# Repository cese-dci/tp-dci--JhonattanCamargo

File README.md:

# TP Diseño de Circuitos Imprsos [CESE 8Co2019 DCI]
## Autor: Jhonattan Camargo
### Alumno revisor: Fabián Sarmiento
### Descripción del proyecto:

El proyecto consiste en la elaboración de uno de los módulos del proyecto final de carrera. El módulo incorpora el integrado LP5012 de Texas Instruments, el cual es un controlador de leds de 12 canales, controlado a través de I2C. El módulo que se propone para el TP final es una adaptación al módulo de evaluación de TI LP5012EVM (http://www.ti.com/lit/ug/slvubb2/slvubb2.pdf) adaptado para ocupar poco espacio e incoporar 2 LEDs RGB y 6 leds individuales.

El repositorio está organizado de la siguiente forma:
  
  - Directorio “doc”: contiene la explicación del circuito, licencia y las revisiones realizadas al diseño.
  - Directorio “info”: contiene hojas de datos, y toda la información relevante como fotos o notas de aplicación.
  - Directorio “pcb”: archivos del proyecto Kicad.
    - Subdirectorio “3dshapes”: contiene los modelos 3D.

### Renders del proyecto:

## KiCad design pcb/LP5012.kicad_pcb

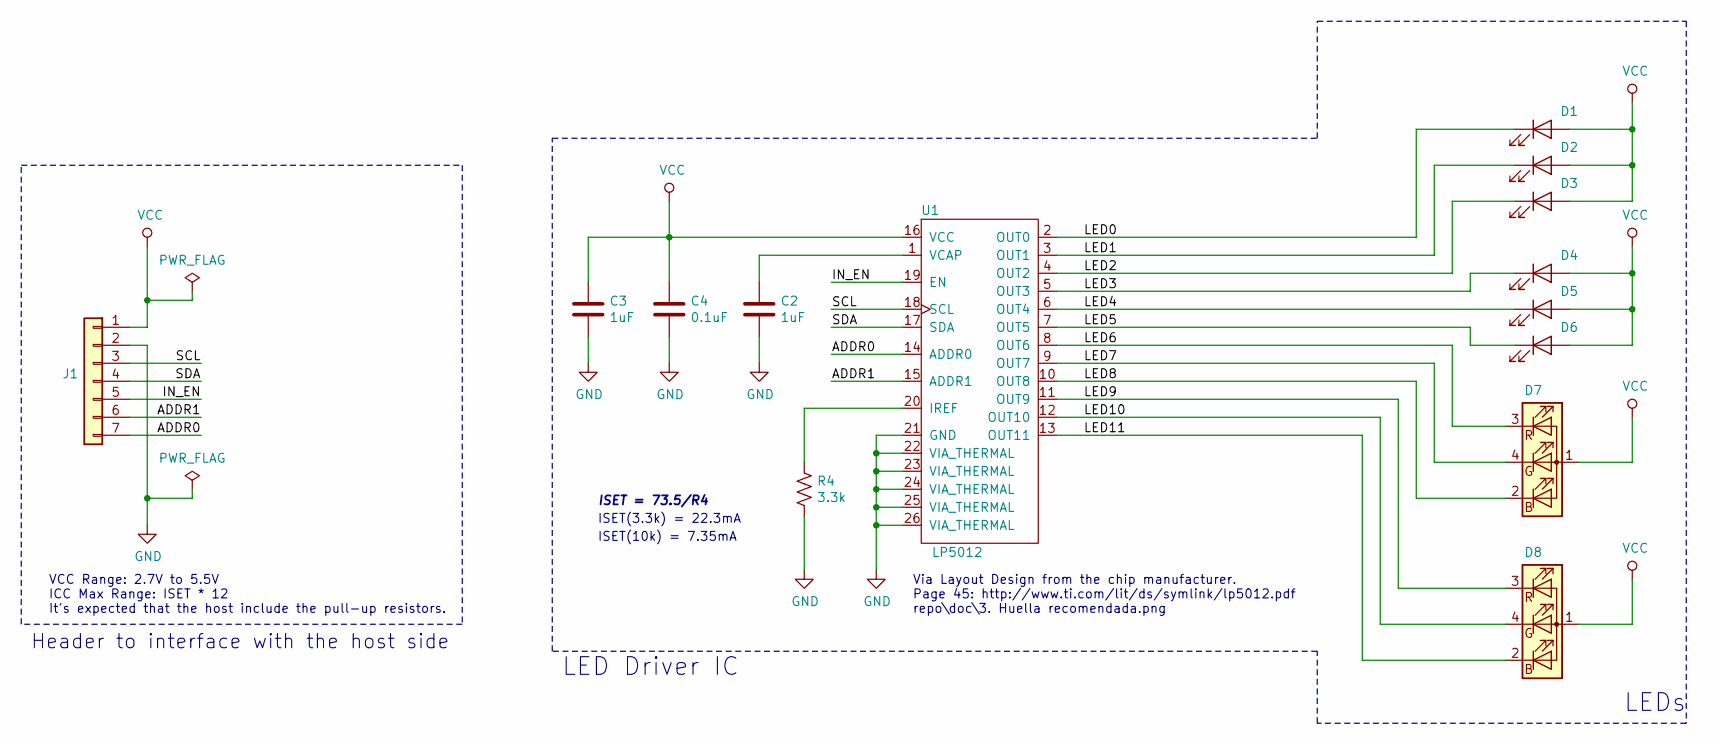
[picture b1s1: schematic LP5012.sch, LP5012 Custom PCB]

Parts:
C2, C3: 1uF; C_0805_2012Metric
C4: 0.1uF; C_0805_2012Metric
D1, D2, D3, D4, D5, D6: LED; LED_0805_2012Metric
D7, D8: LED_RGB; LED_RGB_1210_with3DShape
J1: Main Connector; PinHeader_1x07_P2.54mm_Vertical
R4: 3.3k; R_0805_2012Metric
U1: LP5012

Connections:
/ADDR0: J1.7, U1.14 (ADDR0)
/ADDR1: J1.6, U1.15 (ADDR1)
/IN_EN: J1.5, U1.19 (EN)
/LED0: D1.1 (K), U1.2 (OUT0)
/LED1: D2.1 (K), U1.3 (OUT1)
/LED2: D3.1 (K), U1.4 (OUT2)
/LED3: D4.1 (K), U1.5 (OUT3)
/LED4: D5.1 (K), U1.6 (OUT4)
/LED5: D6.1 (K), U1.7 (OUT5)
/LED6: D7.3 (RK), U1.8 (OUT6)
/LED7: D7.4 (GK), U1.9 (OUT7)
/LED8: D7.2 (BK), U1.10 (OUT8)
/LED9: D8.3 (RK), U1.11 (OUT9)
/LED10: D8.4 (GK), U1.12 (OUT10)
/LED11: D8.2 (BK), U1.13 (OUT11)
/SCL: J1.3, U1.18 (SCL)
/SDA: J1.4, U1.17 (SDA)
GND: C2.2, C3.2, C4.2, J1.2, R4.2, U1.21 (GND), U1.22 (VIA_THERMAL), U1.23 (VIA_THERMAL), U1.24 (VIA_THERMAL), U1.25 (VIA_THERMAL), U1.26 (VIA_THERMAL)
unnamed: C2.1, U1.1 (VCAP)
unnamed: R4.1, U1.20 (IREF)
VCC: C3.1, C4.1, D1.2 (A), D2.2 (A), D3.2 (A), D4.2 (A), D5.2 (A), D6.2 (A), D7.1 (A), D8.1 (A), J1.1, U1.16 (VCC)

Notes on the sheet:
Via Layout Design from the chip manufacturer. Page 45: http://www.ti.com/lit/ds/symlink/lp5012.pdf repo\doc\3. Huella recomendada.png
VCC Range: 2.7V to 5.5V ICC Max Range: ISET * 12 It's expected that the host include the pull-up resistors.
ISET = 73.5/R4
ISET(3.3k) = 22.3mA
Header to interface with the host side
LED Driver IC
LEDs
ISET(10k) = 7.35mA

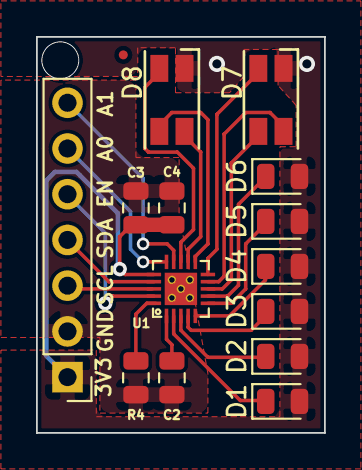
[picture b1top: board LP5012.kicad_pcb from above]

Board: 2 copper layers, 16.0 x 22.0 mm, 15 parts (0 on the bottom side), 21 nets.

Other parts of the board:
FD1: Fiducial_0.5mm_Mask1mm

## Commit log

2019-10-01 Inclusión de Esquemático V1
2019-10-04 Inclusión de la versión custom que se fabricará para el proyecto final
2019-10-04 Inclusion de datasheet del chip y otros archivos
2019-10-04 Corrección de errores y actualizacion de nombres
2019-10-05 Corregidos algunos aspectos del revisor
2019-10-06 Inclusion de PCB
2019-10-06 Avance de ruteo
2019-10-12 Inclusión de avance de PCB
    Inclusión de planos, queda pendiente agregar modelos 3D de agunos componentes
2019-10-12 Corrección de DRCs
2019-10-12 Inclusión de algunos aspectos de la corrección del compañero
2019-10-13 Depuración de archivos sobrantes y estructuración de carpetas
    Se añaden carpetas doc, info y pcb.
    Se limpian archivos que estaban de más.
2019-10-13 Creación de Readme.md
2019-10-13 Inclusión de modelos 3D y modificación de algunas liberías
2019-10-13 Inclusión de renders
2019-10-19 Ligeras modificaciones estéticas
2019-10-19 Inlcusión de notas de fabricación
2019-10-19 Update LP5012.kicad_pcb-bak
2019-10-19 Inclusión de cambios de revisión 2
2019-10-19 Ultimas modificaciones
2019-10-26 Inclusión del agujero requerido
    Inclusión de agujero para sujeción M2
